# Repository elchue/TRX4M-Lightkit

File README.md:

## 🚙 Traxxas TRX-4M Custom Light Controller

Ein maßgeschneidertes, intelligentes Steuergerät (basierend auf dem **ESP32-C6**), um das **originale Traxxas TRX-4M Pro Scale Lichtkit (inkl. Lightbar)** mit 3rd-Party Fernsteuerungen (wie Flysky Noble NB4, Radiomaster, Futaba etc.) und Aftermarket-ESCs weiterverwenden zu können!

Wer seinen TRX-4M auf Brushless (z. B. Furitek) oder eine professionelle Funke umbaut, verliert normalerweise die Funktion des originalen Traxxas-Lichtsets, da dieses fest an die Traxxas ECM-2.5 Einheit gebunden ist. Dieses Projekt ersetzt die Traxxas-Elektronik als "Gehirn" für die Lichter und wertet das System mit smarten Features, Web-Konfiguration und Telemetrie-ähnlicher Auswertung extrem auf.

## ✨ Warum dieses Projekt?
Das originale TRX-4M Lichtkit nutzt adressierbare LEDs (ähnlich dem WS2812-Protokoll), die über eine serielle Datenleitung angesteuert werden. Wie genau wir die proprietären Signale entschlüsselt haben, kannst du in unserer detaillierten [Hardware & Protokoll Dokumentation (Reverse Engineering)](/docs/README.md) nachlesen.

Dieses Modul liest das Signal deines neuen Empfängers aus, berechnet die Fahrphysik und übersetzt sie in Echtzeit für das Traxxas-Lichtset. Du musst nichts abrüsten oder neu verkabeln – das Modul klinkt sich einfach als Übersetzer dazwischen!

## 🚀 Features
* **Multi-Protokoll für 3rd-Party Empfänger:** Unterstützt SBUS, iBUS und klassisches PPM. Ideal für Micro-Empfänger.
* **Smartphone Web-Interface:** Eigener WLAN-Access-Point zur einfachen Konfiguration direkt am Fahrzeug (Deutsch & Englisch). Kein PC auf dem Trail nötig!
* **Perfekte Anpassung an die Funke:**
  * **Volles Channel-Mapping:** Weise Funktionen wie Hauptlicht, Zusatzscheinwerfer und Blinker völlig frei beliebigen Empfängerkanälen zu.
  * **Auto-Trim-Funktion:** Ein Klick im Web-Interface und das Modul speichert den mechanischen Lenk-Offset (Nullpunkt) deiner Funke.
  * **Reverse-Schalter:** Die Laufrichtung jedes Kanals lässt sich direkt in der Software umkehren.
* **Erweiterte Blinker- & Licht-Logik:**
  * **Smart Auto-Cancel:** Blinker schaltet sich wie beim echten Auto ab, wenn du aus der Kurve lenkst.
  * **Blinker-Styles:** Wähle das optische Design (Classic, Soft-Off (Mazda), Soft-On (BMW), Retro Glühlampe).
  * **Regionale Licht-Profile (EU/US):** Verwandle die Optik deines Scalers mit einem Klick:
    * *EU-Style:* Klassisch getrennte Blinker (gelb) und Bremslichter (rot).
    * *US-Style Front:* Vordere Blinker glimmen dauerhaft gedimmt als orange Sidemarker (Standlicht) und pulsieren beim Blinken.
    * *US-Style Komplett:* Front-Sidemarker kombiniert mit typisch amerikanischem Heck (das rote Bremslicht blinkt im Takt, die gelben Blinker bleiben deaktiviert).
* **Adaptives Bremslicht (ESS):** Erkennt echte Vollbremsungen über den Gashebel und lässt das Bremslicht realistisch flackern. Danach schaltet sich automatisch der Warnblinker ein.
* **ESC-Kompatibilität & Fahrlogik:** Drei wählbare Profile für die perfekte Erkennung von Bremse und Rückfahrlicht:
  * *Standard:* Klassischer RC-Regler (Doppelklick für Rückwärts).
  * *Crawler (FOC):* Drag-Brake Erkennung und direkter Übergang in den Rückwärtsgang.
  * *Real-Car (Getriebe):* Manuelle Gangschaltung (Vorwärts / Rückwärts) über einen separaten AUX-Kanal für den ultimativen Scale-Realismus.
* **Standby & Parklicht:** Dimmt die Scheinwerfer nach definierter Inaktivität automatisch ab, um Strom zu sparen und Hitzestau zu vermeiden. Generelle Master-Helligkeit im Web-UI einstellbar.

## 🛠 Hardware & Verkabelung
Das Projekt läuft auf einem **Seeed Studio XIAO ESP32-C6** (oder ähnlichen, kompakten ESP32-Boards), da dieser klein genug ist, um problemlos in den TRX-4M zu passen.
* **Eingang:** Der ESP32 wird per 3-Pin-Kabel mit dem Empfänger verbunden (Strom, GND, Signal-Pin für SBUS/iBUS/PPM).
* **Ausgänge (2-Kanal System):** Die Ansteuerung der Traxxas-LEDs erfolgt über zwei getrennte Datenleitungen am ESP32.
  * **Kanal 1 (Main):** Übernimmt die komplette Basis-Fahrzeugbeleuchtung (Scheinwerfer, Rücklichter, Blinker).
  * **Kanal 2 (Aux):** Ist exklusiv für Zusatzscheinwerfer (z. B. Lightbars oder Roof-Lights) reserviert und lässt sich separat schalten.

*(Detaillierte Pin-Belegung und Schaltpläne für den Anschluss des Traxxas-Kabelbaums findest du im Wiki / in den Code-Kommentaren).*

## 💻 Installation (PlatformIO)
1. Repository klonen: 
    ``` bash
    git clone https://github.com/DEIN_NAME/trx4m-light-controller.git
    ```
2. Ordner in **VS Code** (mit PlatformIO) öffnen.
3. ESP32-C6 über USB-C anschließen.
4. Auf "Upload" klicken – PlatformIO kompiliert den Code und flasht den Chip automatisch.

## 📱 Konfiguration im Fahrzeug
1. TRX-4M einschalten. Der ESP32 öffnet ein WLAN-Netzwerk (z.B. ProScale-Config).
2. Smartphone verbinden und [http://192.168.4.1](http://192.168.4.1) im Browser öffnen.
3. Kanäle zuweisen, Blinker-Verhalten wählen und ggf. die Lenkung über den "Auto-Trim"-Button exakt nullen.
4. Speichern, Neustart abwarten – fertig für den Trail!

## 📄 Lizenz
Dieses Projekt ist unter der GNU General Public License v3.0 (GPLv3) lizenziert. Der Code ist Open Source. Details siehe LICENSE-Datei.

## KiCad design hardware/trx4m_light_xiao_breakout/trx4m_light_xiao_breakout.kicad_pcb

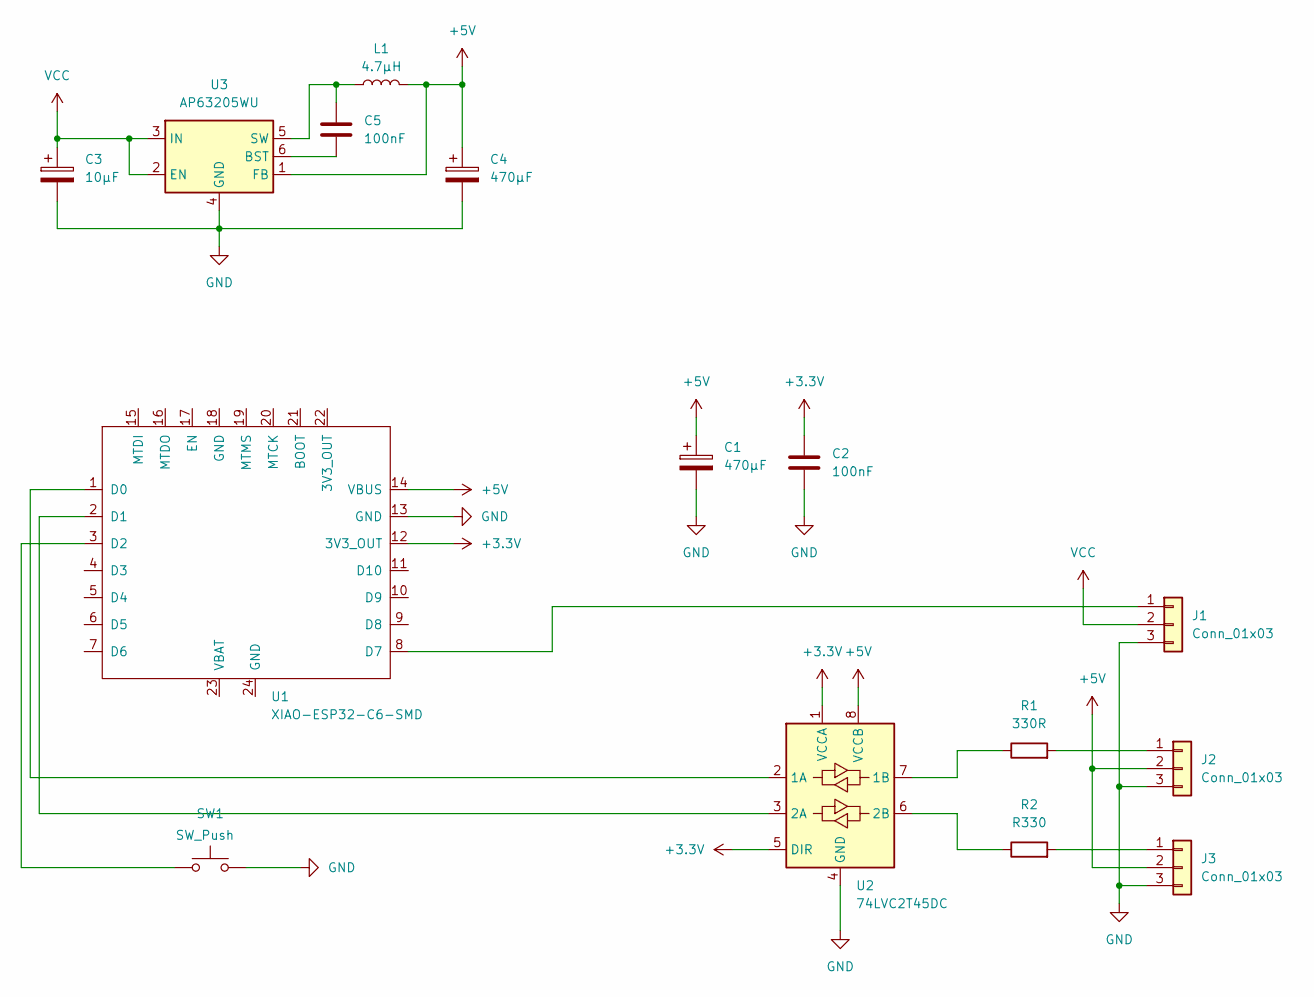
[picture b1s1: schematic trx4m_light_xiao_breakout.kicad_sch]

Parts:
C1, C4: 470µF; CP_EIA-7343-20_Kemet-V; LCSC C49332972
C2, C5: 100nF; C_0805_2012Metric; LCSC C28233
C3: 10µF; C_0805_2012Metric; LCSC C15850
J1, J2, J3: Conn_01x03; PinHeader_1x03_P2.54mm_Vertical
L1: 4.7µH; L_Ferrocore_DLG-0403; LCSC C2879693
R1: 330R; R_0805_2012Metric; LCSC C17630
R2: R330; R_0805_2012Metric; LCSC C17630
SW1: SW_Push; SW_Tactile_SPST_NO_Straight_CK_PTS636Sx25SMTRLFS; LCSC C2689642
U1: XIAO-ESP32-C6-SMD; XIAO-14P-Add-On
U2: 74LVC2T45DC; VSSOP-8_2.3x2mm_P0.5mm; LCSC C15741
U3: AP63205WU; TSOT-23-6; LCSC C2071056

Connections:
+3.3V: C2.1, U1.12 (3V3_OUT), U2.1 (VCCA), U2.5 (DIR)
+5V: C1.1, C4.1, J2.2, J3.2, L1.2, U1.14 (VBUS), U2.8 (VCCB), U3.1 (FB)
GND: C1.2, C2.2, C3.2, C4.2, J1.3, J2.3, J3.3, SW1.2, U1.13 (GND), U2.4 (GND), U3.4 (GND)
unnamed: J1.1, U1.8 (D7)
unnamed: J2.1, R1.2
unnamed: J3.1, R2.2
unnamed: U1.1 (D0), U2.2 (1A)
unnamed: U1.2 (D1), U2.3 (2A)
unnamed: SW1.1, U1.3 (D2)
unnamed: R1.1, U2.7 (1B)
unnamed: R2.1, U2.6 (2B)
unnamed: C5.2, U3.6 (BST)
unnamed: C5.1, L1.1, U3.5 (SW)
VCC: C3.1, J1.2, U3.2 (EN), U3.3 (IN)

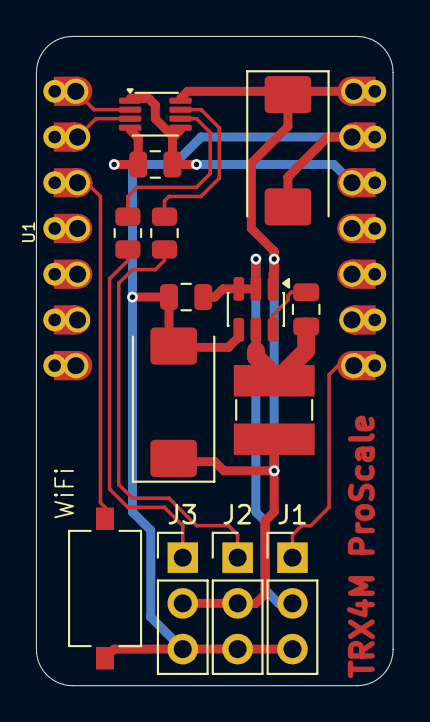
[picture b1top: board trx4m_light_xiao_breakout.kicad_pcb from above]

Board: 2 copper layers, 19.8 x 36.1 mm, 15 parts (0 on the bottom side), 14 nets.

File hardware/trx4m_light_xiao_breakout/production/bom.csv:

Designator,Footprint,Quantity,Value,LCSC Part #
"C1, C4",CP_EIA-7343-20_Kemet-V,2,470µF,C49332972
"C2, C5",0805,2,100nF,C28233
C3,0805,1,10µF,C15850
"J1, J2, J3",PinHeader_1x03_P2.54mm_Vertical,3,Conn_01x03,
L1,L_Ferrocore_DLG-0403,1,4.7µH,C2879693
R1,0805,1,330R,C17630
R2,0805,1,R330,C17630
SW1,SW_Tactile_SPST_NO_Straight_CK_PTS636Sx25SMTRLFS,1,SW_Push,C2689642
U1,XIAO-14P-Add-On,1,XIAO-ESP32-C6-SMD,
U2,VSSOP-8_2.3x2mm_P0.5mm,1,74LVC2T45DC,C15741
U3,TSOT-23-6,1,AP63205WU,C2071056

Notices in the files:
README.md:
License: GPL v3
